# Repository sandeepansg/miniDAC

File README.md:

<h1 align="center"> Arduino miniDAC Module </h1> <br>

## Table of Contents
- [About](#about)
- [Social](#social)
- [License](#license)
- [Acknowledgments](#acknowledgments)

## About

**Arduino miniDAC Module** is a unipolar digital to analog converter (DAC) module built arround [LTC®2633](http://www.linear.com/product/LTC2633), which is a family of dual 12-, 10-, and 8-bit voltage-output DACs with an integrated, high accuracy, low drift reference in an 8-lead TSOT-23 package.
<br>These DACs communicate via a 2-wire I2C-compatible serial interface operating in both the standard mode (clock rate of 100kHz) and the fast mode (clock rate of 400kHz).
<br>It is compatible with both 3.3V and 5V logic levels and uses [LTC2633](https://github.com/TamojitSaha/LTC2633) library developed by [Tamojit Saha](http://tamojit.tk) and [Sandeepan Sengupta](http://sandeepan.info)
<p align="center">
  &nbsp
  &nbsp
  &nbsp
</p>
<p align="center">
  &nbsp 
  &nbsp
</p>

## Social
Connect us here:
<br><br>
 <br>
 
<p> 
or <a href ="https://github.com/TamojitSaha/LTC2633/issues/new/">file an issue</a>. Feature requests are always welcome.</p>

## License
Contents of this repository are realeased under [CC-BY-NC-SA 4.0](./LICENSE.md) <br>

## Acknowledgments
Thanks to the contributors! :wink:

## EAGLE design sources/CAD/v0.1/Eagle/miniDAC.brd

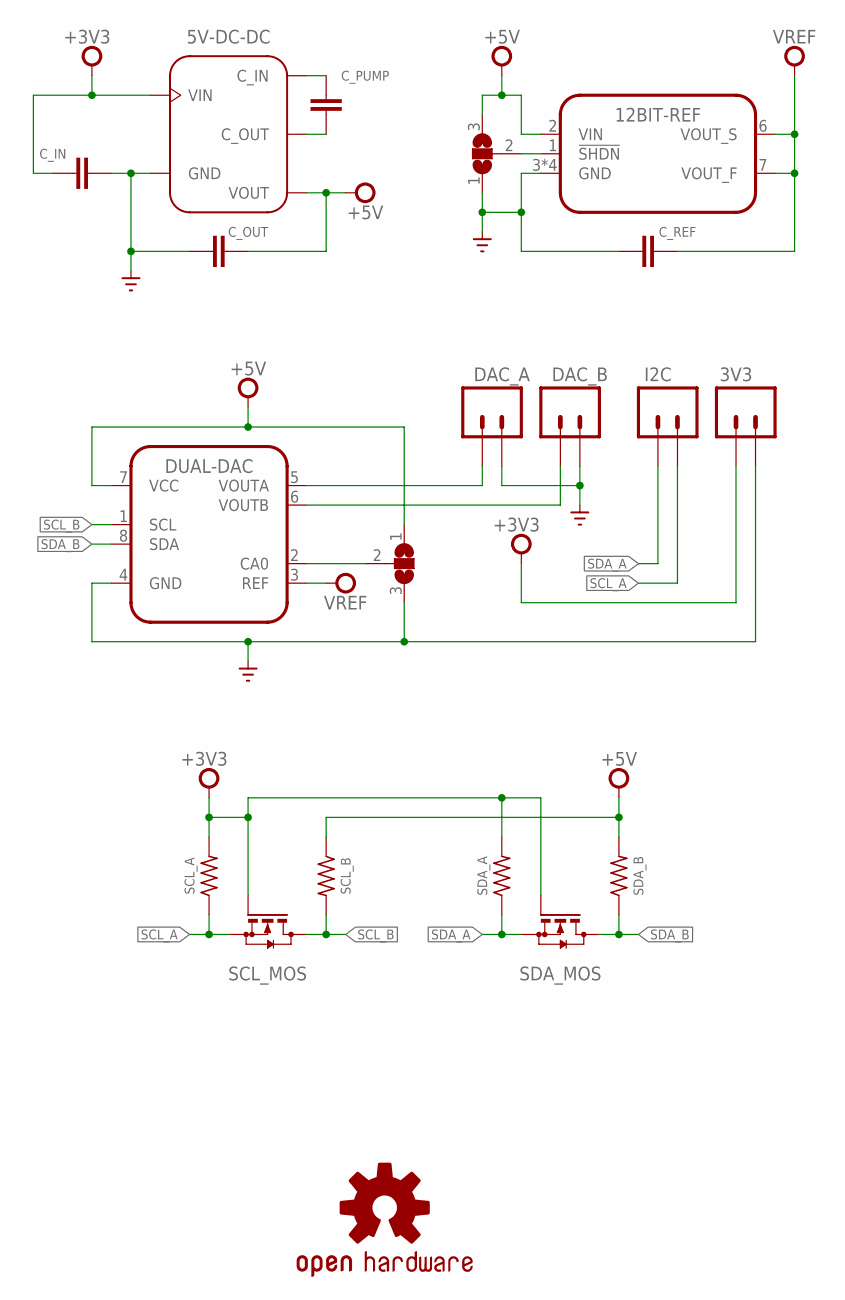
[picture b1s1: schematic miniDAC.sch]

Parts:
3V3: M02LOCK; 1X02_LOCK
5V-DC-DC: LTC1517CS5-5#PBF; SOT-23_S5
12BIT-REF: LTC6655CHMS8-5PBF; SOP65P490X110-8N
ADDR_SEL: SJ2WW; SJ_2W
C_IN: 3.3uF; C1206K
C_OUT: 6.8uF; C1206K
C_PUMP: 0.1uF; C1206K
C_REF: 10uF; C1206K
DAC_A: M025MM; SCREWTERMINAL-5MM-2
DAC_B: M025MM; SCREWTERMINAL-5MM-2
DUAL-DAC: LTC2633CTS8-HZ8PBF; SOT65P280X100-8N
I2C: M02LOCK; 1X02_LOCK
OSHW: OSHW-LOGOL; OSHW-LOGO-L
REF_SEL: SJ2WW; SJ_2W
SCL_A: 2.7K; M1206
SCL_B: 1.3K; M1206
SCL_MOS: BSS123; SOT23
SDA_A: 2.7K; M1206
SDA_B: 1.3K; M1206
SDA_MOS: BSS123; SOT23

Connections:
!SHDN: 12BIT-REF.1 (!SHDN), REF_SEL.2
+3V3: 3V3.1, 5V-DC-DC.VIN, C_IN.1, SCL_A.2, SCL_MOS.1 (G), SDA_A.2, SDA_MOS.1 (G)
+5V: 5V-DC-DC.VOUT, 12BIT-REF.2 (VIN), ADDR_SEL.1, C_OUT.2, DUAL-DAC.7 (VCC), REF_SEL.3, SCL_B.1, SDA_B.2
CA0: ADDR_SEL.2, DUAL-DAC.2 (CA0)
C_IN: 5V-DC-DC.C_OUT (C_IN), C_PUMP.1
C_OUT: 5V-DC-DC.C_IN (C_OUT), C_PUMP.2
DAC_A: DAC_A.2, DUAL-DAC.5 (VOUTA)
DAC_B: DAC_B.2, DUAL-DAC.6 (VOUTB)
GND: 3V3.2, 5V-DC-DC.GND, 12BIT-REF.3 (GND), 12BIT-REF.4 (GND), 12BIT-REF.5 (GND), 12BIT-REF.8 (GND), ADDR_SEL.3, C_IN.2, C_OUT.1, C_REF.2, DAC_A.1, DAC_B.1, DUAL-DAC.4 (GND), REF_SEL.1
SCL_A: I2C.2, SCL_A.1, SCL_MOS.2 (S)
SCL_B: DUAL-DAC.1 (SCL), SCL_B.2, SCL_MOS.3 (D)
SDA_A: I2C.1, SDA_A.1, SDA_MOS.2 (S)
SDA_B: DUAL-DAC.8 (SDA), SDA_B.1, SDA_MOS.3 (D)
VREF: 12BIT-REF.6 (VOUT_S), 12BIT-REF.7 (VOUT_F), C_REF.1, DUAL-DAC.3 (REF)

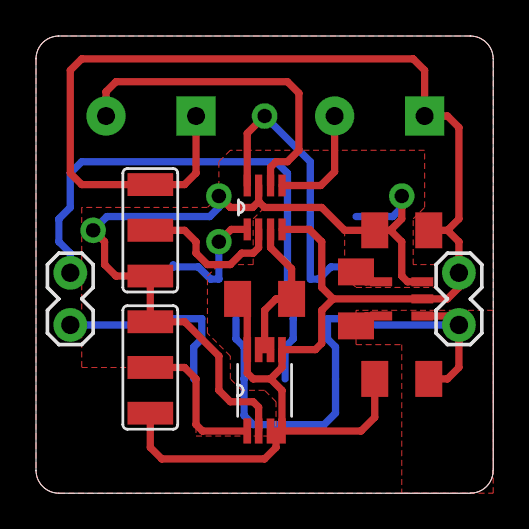
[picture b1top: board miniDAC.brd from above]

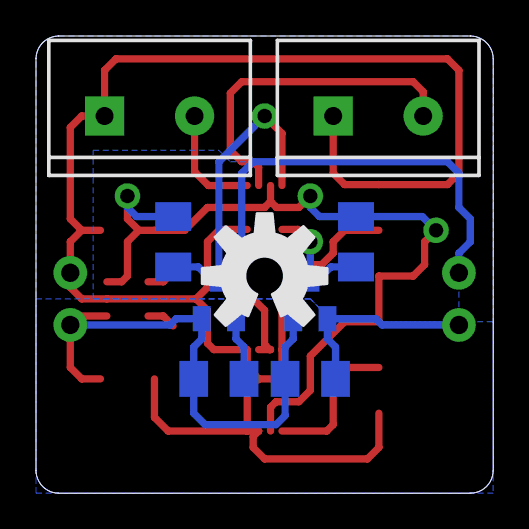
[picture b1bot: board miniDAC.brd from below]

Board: 2 copper layers, 25.4 x 25.4 mm, 20 parts (9 on the bottom side), 14 nets.

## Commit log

2018-01-02 Bulk Upload
    Uploaded everything
2018-01-02 Added ZIP library
    Arduino library manager compatible zip file added
2018-01-02 fixed path
2018-01-02 rename path
2018-01-16 Create README.md
    Added README.md
2018-01-16 Update README.md
    Updated README.md

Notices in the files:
parts and their libraries:
SparkFun-Aesthetics: Licensing: CC v3.0 Share-Alike You are welcome to use this library for commercial purposes.
